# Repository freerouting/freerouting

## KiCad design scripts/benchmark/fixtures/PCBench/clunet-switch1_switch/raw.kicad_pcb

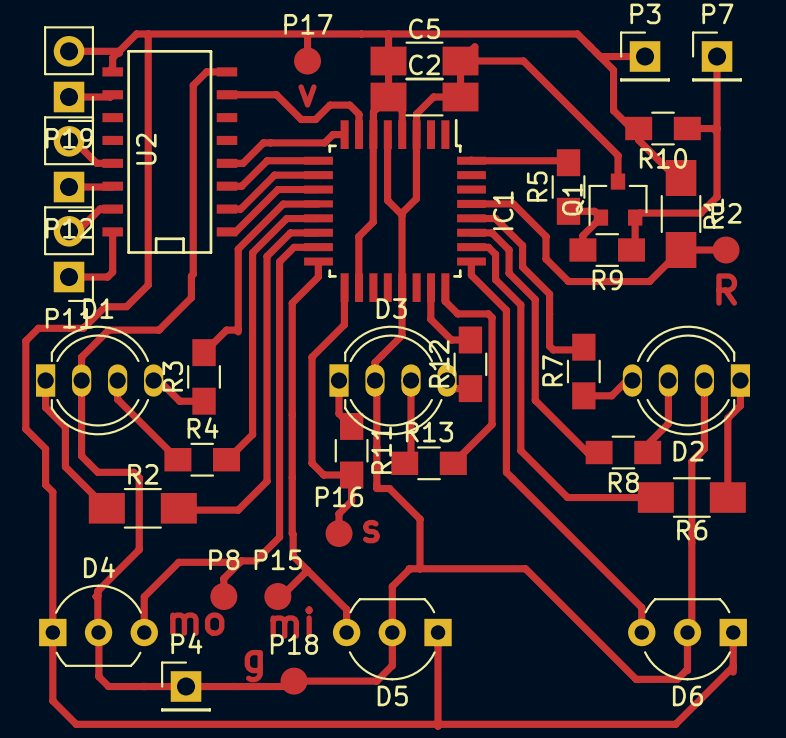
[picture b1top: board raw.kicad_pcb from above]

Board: 2 copper layers, 36 parts (0 on the bottom side), 37 nets.

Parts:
C2: 10mkf; C_1206_HandSoldering
C5: C_Small; C_1206_HandSoldering
D1, D2, D3: Led1; LED_D5.0mm-4-LL
D4, D5, D6: AH201; TO-92_Inline_Wide
IC1: ATMEGA8A-A; TQFP-32_7x7mm_Pitch0.8mm-LUT
P2: Reset; Measurement_Point_Round-SMD-Pad_Small
P3: Vcc; Socket_Strip_Straight_1x01_Pitch2.54mm
P4: Gnd; Socket_Strip_Straight_1x01_Pitch2.54mm
P7: Clunet; Socket_Strip_Straight_1x01_Pitch2.54mm
P8: CON_MOS; Measurement_Point_Round-SMD-Pad_Small
P11: R1_; Socket_Strip_Straight_1x02_Pitch2.54mm
P12: R2_; Socket_Strip_Straight_1x02_Pitch2.54mm
P15: CON_MIS; Measurement_Point_Round-SMD-Pad_Small
P16: CON_SCK; Measurement_Point_Round-SMD-Pad_Small
P17: Vcc_Prog; Measurement_Point_Round-SMD-Pad_Small
P18: Gnd_Prog; Measurement_Point_Round-SMD-Pad_Small
P19: SPK; Socket_Strip_Straight_1x02_Pitch2.54mm
Q1: PNP BC858; SOT-23
R1: 1.5K; R_1206_HandSoldering
R2, R6: 470R; R_1206_HandSoldering
R3, R4, R7, R8, R11, R12, R13: 470R; R_0805_HandSoldering
R5: 2.2K; R_0805_HandSoldering
R9: 22K; R_0805_HandSoldering
R10: 560R; R_0805_HandSoldering
U2: ULN2003-norm; SO-16-N

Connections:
/LED1_1: IC1.14, R2.2
/LED1_2: IC1.13, R4.2
/LED1_3: IC1.12, R3.2
/LED2_1: IC1.17, P16.1, R11.2
/LED2_2: IC1.23, R12.2
/LED2_3: IC1.24, R13.2
/LED3_1: IC1.26, R6.2
/LED3_2: IC1.27, R8.2
/LED3_3: IC1.28, R7.2
/R1_1: IC1.11, U2.1
/R1_2: IC1.10, U2.2
/R2_1: IC1.9, U2.3
/R2_2: IC1.8, U2.4
/SW1: D4.3, IC1.15, P8.1
/SW2: D5.3, IC1.16, P15.1
/SW3: D6.3, IC1.25
/spk: IC1.7, U2.7
GND: C2.2, C5.2, D1.2, D2.2, D3.2, D4.2, D5.2, D6.2, IC1.3, IC1.5, IC1.21, P4.1, P18.1, Q1.3, U2.8
unnamed: D1.1, R2.1
unnamed: D1.3, R4.1
unnamed: D1.4, R3.1
unnamed: D2.1, R6.1
unnamed: D2.3, R8.1
unnamed: D2.4, R7.1
unnamed: D3.1, R11.1
unnamed: D3.3, R13.1
unnamed: D3.4, R12.1
unnamed: IC1.29, P2.1, R1.2
unnamed: IC1.32, R5.2
unnamed: P11.1, U2.16
unnamed: P11.2, U2.15
unnamed: P12.1, U2.14
unnamed: P12.2, U2.13
unnamed: P19.1, U2.10
unnamed: Q1.1, R5.1, R9.2
VCC: C2.1, C5.1, D4.1, D5.1, D6.1, IC1.4, IC1.6, IC1.18, P3.1, P17.1, P19.2, R1.1, R10.2, U2.9
clunet: P7.1, Q1.2, R9.1, R10.1

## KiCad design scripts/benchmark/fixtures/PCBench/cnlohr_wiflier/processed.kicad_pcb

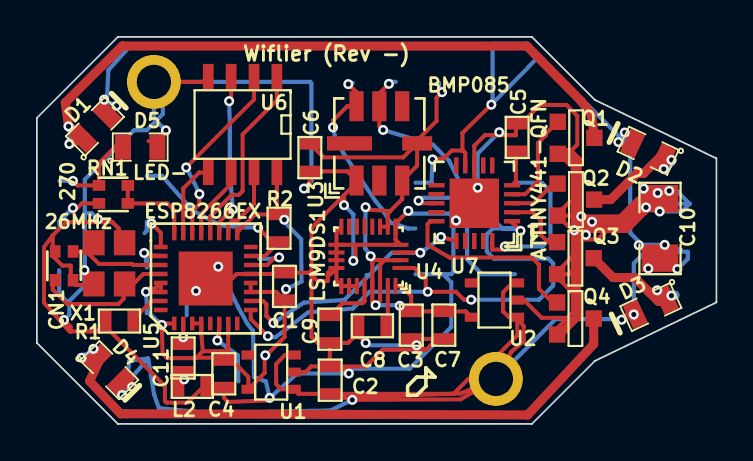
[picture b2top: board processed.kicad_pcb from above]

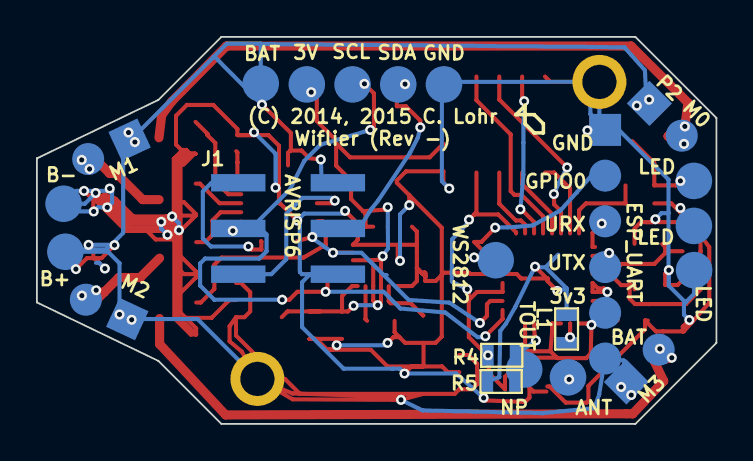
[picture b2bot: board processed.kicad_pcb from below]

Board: 2 copper layers, 37.8 x 21.5 mm, 57 parts (22 on the bottom side), 38 nets.

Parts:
C1, C2, C3: 10uF; SM0603
C4: 1uF; SM0603
C5: 1u; SM0603
C6, C7, C8: .1u; SM0603
C9: 10nF; SM0603
C10: 100uF; SM1206
C11: 5.6pF; SM0603
CN1: 10p; NETWORK0606
D1, D2, D3, D4: 20V_500mA; SM0805
D5: LED-; SM0805
J1: AVRISP6; RIBBON6SMT
L1, L2: NP; SM0603
P1: WS2812; .1SMTPIN
P2: M0; SMT_1x2
P3: M1; SMT_1x2
P4: M2; SMT_1x2
P5: M3; SMT_1x2
P6: ANT; .1SMTPIN
P7, P8: HOLE-1.9MM
P9: SDA; .1SMTPIN
P10: SCL; .1SMTPIN
P11: 3V; .1SMTPIN
P12: GND; .1SMTPIN
P13, P14, P15: LED; .1SMTPIN
P16: BAT; .1SMTPIN
P17: TOUT; .1SMTPIN
P21: B+; .1SMTPIN
P24: B-; .1SMTPIN
P32: ESP_UART; SMT_1x6
Q1, Q2, Q3, Q4: 7A_20V; SOT23GDS
R1, R2, R4: 12k; SM0603
R5: NP; SM0603
RN1: 270; NETWORK0606
U1, U2: MCP1824/3.0; SOT23-5
U3: BMP085
U4: LSM9DS1; LGA-24B
U5: ESP8266EX; QFN32
U6: W25Q80DV; SO8E
U7: ATTINY441-QFN; QFN20
X1: 26MHz; XTAL4P

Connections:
+3.3V: C1.1, C4.1, P32.5, R2.2, R4.1, U1.5, U5.1, U5.3, U5.4, U5.7, U5.11, U5.12, U5.17, U5.29, U5.30, U6.8
+3.3VP: C3.1, C6.2, C7.1, P11.1, U2.5, U3.3, U3.4, U4.1, U4.3, U4.7, U4.8, U4.22, U4.23
+BATT: C2.1, C10.1, D1.2, D2.2, D3.2, D4.2, J1.2, P2.1, P3.1, P4.1, P5.1, P8.1, P16.1, P21.1, P32.6, U1.1, U1.3, U2.1, U2.3, U7.9
AVRMISO: J1.1, U7.20
AVRRST: J1.5, U7.13
GND: C1.2, C2.2, C3.2, C4.2, C5.1, C6.1, C7.2, C8.1, C9.1, C10.2, CN1.2, CN1.3, D5.2, J1.6, L1.2, L2.2, P7.1, P12.1, P15.1, P24.1, P32.1, Q1.S, Q2.S, Q3.S, Q4.S, R1.1, R5.2, U1.2, U2.2, U3.1, U4.5, U4.6, U4.13, U4.14, U4.15, U4.16, U4.17, U4.18, U4.19, U4.20, U5.13, U5.33, U6.4, U7.8, U7.21, X1.3, X1.4
GP5: RN1.1, RN1.3, U5.24
GPIO0: P32.2, R2.1, U5.15
GPIO2: P1.1, U5.14
M0P: D1.1, P2.2, Q1.D
M1P: D2.1, P3.2, Q2.D
M2P: D3.1, P4.2, Q3.D
M3P: D4.1, P5.2, Q4.D
MTR0: Q1.G, U7.4
MTR1: Q2.G, U7.3
MTR2: Q3.G, U7.2
MTR3: Q4.G, U7.15
unnamed: C11.1, L1.1, U5.2
unnamed: C11.2, L2.1, P6.1
unnamed: CN1.1, U5.28, X1.2
unnamed: R1.2, U5.31
unnamed: CN1.4, U5.27, X1.1
unnamed: C8.2, U4.24
unnamed: C9.2, U4.21
unnamed: P13.1, RN1.2
unnamed: D5.1, P14.1, RN1.4
unnamed: C5.2, U7.5
unnamed: U5.22, U6.2
unnamed: U5.23, U6.5
unnamed: U5.19, U6.3
unnamed: U5.18, U6.7
unnamed: U5.20, U6.1
unnamed: U5.21, U6.6
SCL: J1.3, P10.1, U3.6, U4.2, U5.9, U7.1
SDA: J1.4, P9.1, U3.7, U4.4, U5.10, U7.16
TOUT: P17.1, R4.2, R5.1, U5.6
URX: P32.3, U5.25
UTX: P32.4, U5.26

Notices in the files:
scripts/benchmark/fixtures/PCBench/cnlohr_wiflier/processed.kicad_pcb:
(C) 2014, 2015 C. Lohr
